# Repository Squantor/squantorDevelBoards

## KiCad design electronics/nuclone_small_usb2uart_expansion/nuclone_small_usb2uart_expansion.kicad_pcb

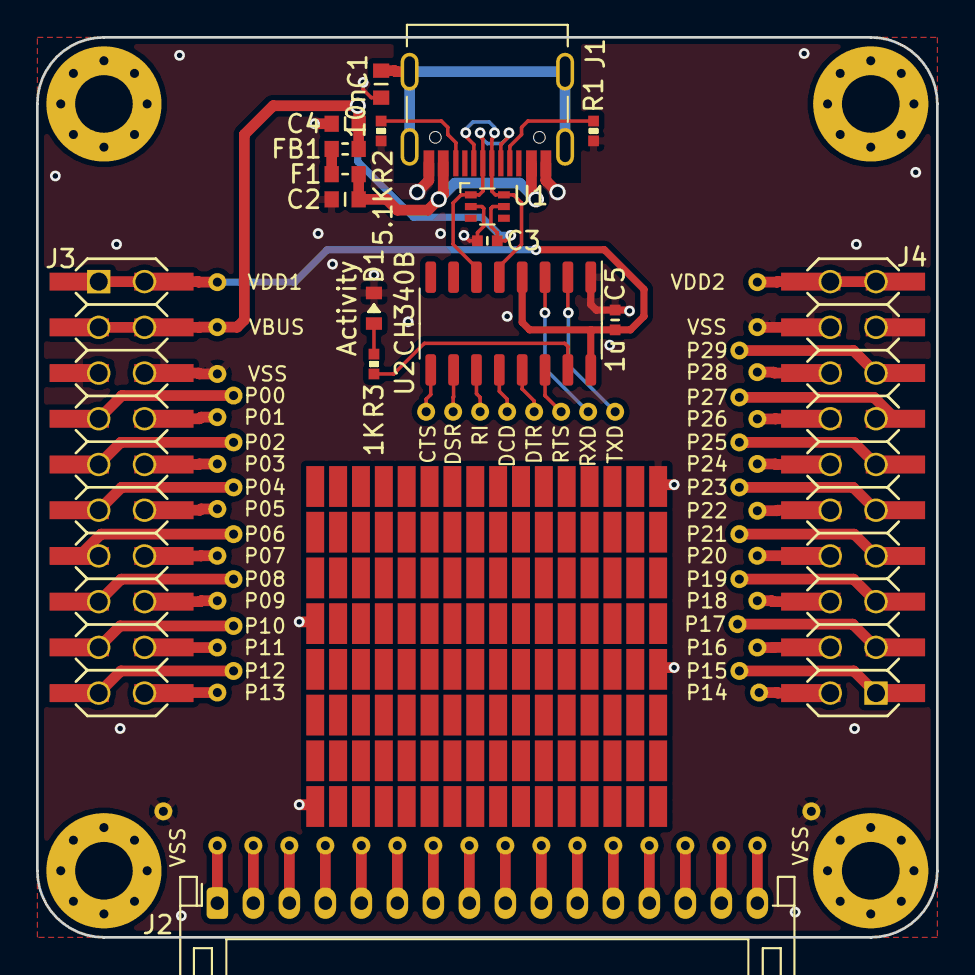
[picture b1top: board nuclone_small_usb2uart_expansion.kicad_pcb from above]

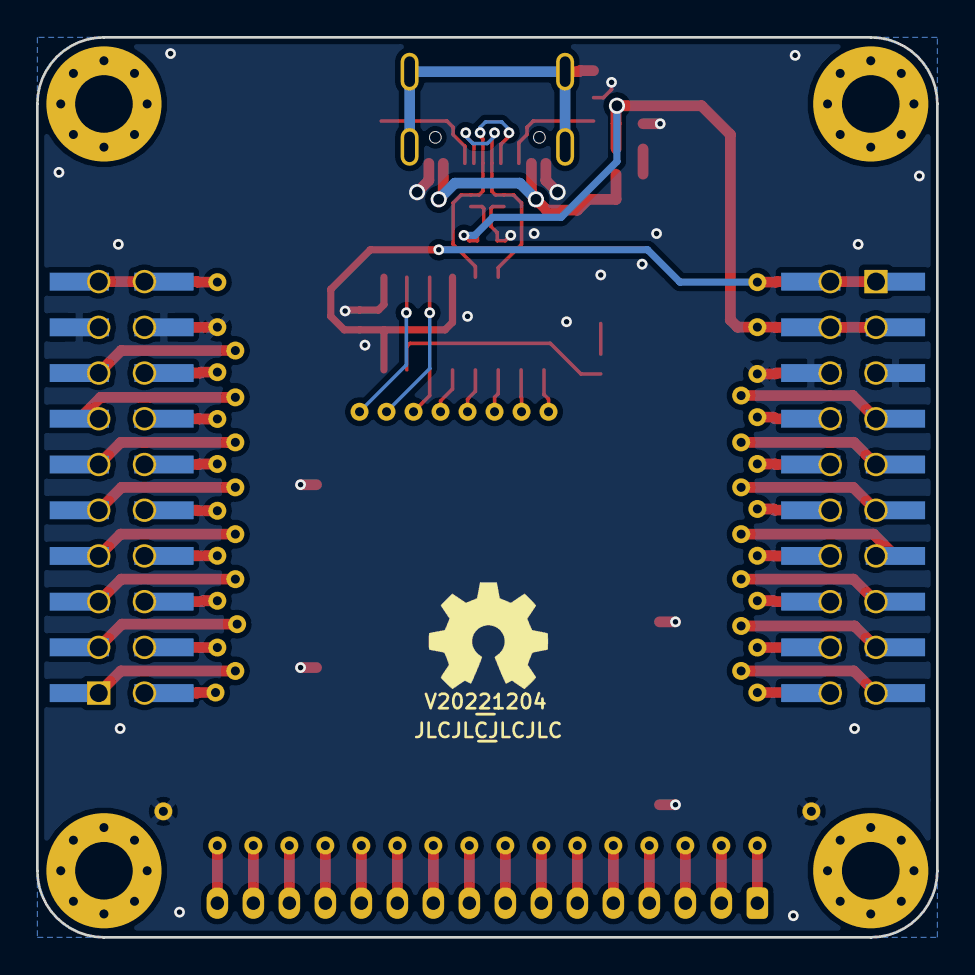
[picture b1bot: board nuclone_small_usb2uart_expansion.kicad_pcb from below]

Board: 2 copper layers, 50.0 x 50.0 mm, 89 parts (3 on the bottom side), 67 nets.

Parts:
C1: 10n; C_0603
C2: 100n; C_0603
C3, C5: 1u; C_0402
C4: 10u; C_0603
D1: Activity; LED_0603_hand
F1: 0.5A; F_0603_hand
FB1: 600; L_0603
H1, H2, H3, H4: MountingHole; MountingHole_3.2mm_M3_Pad_Via
J1: USB-C_PD_USB; USB-C-HRO-31-M-12
J2: Conn_01x16; JST_PH_S16B-PH-K_1x16_P2.00mm_Horizontal
J3: nuclone_small_left; nuclone_small_left_stacked
J4: nuclone_small_right; nuclone_small_right_stacked
J5, J6, J7, J8: 127; proto-SMD-0127-08X08-P010X020+pad
N1: OHWLOGO; OSHW-Symbol_6.7x6mm_SilkScreen
N2: V20221204; Label_Generic
N3: JLCJLCJLCJLC; Label_Generic
R1, R2: 5.1K; R_0402_hand
R3: 1K; R_0402_hand
TP1: VDD1; TestPoint_hole_H05R10_small_text
TP2: VBUS; TestPoint_hole_H05R10_small_text
TP3, TP19, TP60, TP61: VSS; TestPoint_hole_H05R10_small_text
TP4: P00; TestPoint_hole_H05R10_small_text
TP5: P01; TestPoint_hole_H05R10_small_text
TP6: P02; TestPoint_hole_H05R10_small_text
TP7: P03; TestPoint_hole_H05R10_small_text
TP8: P04; TestPoint_hole_H05R10_small_text
TP9: P05; TestPoint_hole_H05R10_small_text
TP10: P06; TestPoint_hole_H05R10_small_text
TP11: P07; TestPoint_hole_H05R10_small_text
TP12: P08; TestPoint_hole_H05R10_small_text
TP13: P09; TestPoint_hole_H05R10_small_text
TP14: P10; TestPoint_hole_H05R10_small_text
TP15: P11; TestPoint_hole_H05R10_small_text
TP16: P12; TestPoint_hole_H05R10_small_text
TP17: P13; TestPoint_hole_H05R10_small_text
TP18: VDD2; TestPoint_hole_H05R10_small_text
TP20: P29; TestPoint_hole_H05R10_small_text
TP21: P28; TestPoint_hole_H05R10_small_text
TP22: P27; TestPoint_hole_H05R10_small_text
TP23: P26; TestPoint_hole_H05R10_small_text
TP24: P25; TestPoint_hole_H05R10_small_text
TP25: P24; TestPoint_hole_H05R10_small_text
TP26: P23; TestPoint_hole_H05R10_small_text
TP27: P22; TestPoint_hole_H05R10_small_text
TP28: P21; TestPoint_hole_H05R10_small_text
TP29: P20; TestPoint_hole_H05R10_small_text
TP30: P19; TestPoint_hole_H05R10_small_text
TP31: P18; TestPoint_hole_H05R10_small_text
TP32: P17; TestPoint_hole_H05R10_small_text
TP33: P16; TestPoint_hole_H05R10_small_text
TP34: P15; TestPoint_hole_H05R10_small_text
TP35: P14; TestPoint_hole_H05R10_small_text
TP36: TXD; TestPoint_hole_H05R10_small_text
TP37: RXD; TestPoint_hole_H05R10_small_text
TP38: RTS; TestPoint_hole_H05R10_small_text
TP39: DTR; TestPoint_hole_H05R10_small_text
TP40: DCD; TestPoint_hole_H05R10_small_text
TP41: RI; TestPoint_hole_H05R10_small_text
TP42: DSR; TestPoint_hole_H05R10_small_text
TP43: CTS; TestPoint_hole_H05R10_small_text
TP44: PH1; TestPoint_hole_H05R10_small_text
TP45: PH2; TestPoint_hole_H05R10_small_text
TP46: PH3; TestPoint_hole_H05R10_small_text
TP47: PH4; TestPoint_hole_H05R10_small_text
TP48: PH5; TestPoint_hole_H05R10_small_text
TP49: PH6; TestPoint_hole_H05R10_small_text
TP50: PH7; TestPoint_hole_H05R10_small_text
TP51: PH8; TestPoint_hole_H05R10_small_text
TP52: PH9; TestPoint_hole_H05R10_small_text
TP53: PH10; TestPoint_hole_H05R10_small_text
TP54: PH11; TestPoint_hole_H05R10_small_text
TP55: PH12; TestPoint_hole_H05R10_small_text
TP56: PH13; TestPoint_hole_H05R10_small_text
TP57: PH14; TestPoint_hole_H05R10_small_text
TP58: PH15; TestPoint_hole_H05R10_small_text
TP59: PH16; TestPoint_hole_H05R10_small_text
U1: TPESD0504C6; SOT363-ONsemi
U2: CH340B; SO-16_3.9x9.9mm_P1.27mm

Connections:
/CC1: J1.A5 (CC1), R1.2
/CC2: J1.B5 (CC2), R2.2
/CTS: TP43.1, U2.9 (CTS#)
/DCD: TP40.1, U2.12 (DCD#)
/DN: J1.A7 (DN1), J1.B7 (DN2), U1.1 (IO_1), U2.6 (UD-)
/DP: J1.A6 (DP1), J1.B6 (DP2), U1.6 (IO_4), U2.5 (UD+)
/DSR: TP42.1, U2.10 (DSR#)
/DTR: TP39.1, U2.13 (DTR#)
/GPIO_00: J3.7 (GPIO_00), TP4.1
/GPIO_01: J3.8 (GPIO_01), TP5.1
/GPIO_02: J3.9 (GPIO_02), TP6.1
/GPIO_03: J3.10 (GPIO_03), TP7.1
/GPIO_04: J3.11 (GPIO_04), TP8.1
/GPIO_05: J3.12 (GPIO_05), TP9.1
/GPIO_06: J3.13 (GPIO_06), TP10.1
/GPIO_07: J3.14 (GPIO_07), TP11.1
/GPIO_08: J3.15 (GPIO_08), TP12.1
/GPIO_09: J3.16 (GPIO_09), TP13.1
/GPIO_10: J3.17 (GPIO_10), TP14.1
/GPIO_11: J3.18 (GPIO_11), TP15.1
/GPIO_12: J3.19 (GPIO_12), TP16.1
/GPIO_13: J3.20 (GPIO_13), TP17.1
/GPIO_14: J4.2 (GPIO_14), TP35.1
/GPIO_15: J4.1 (GPIO_15), TP34.1
/GPIO_16: J4.4 (GPIO_16), TP33.1
/GPIO_17: J4.3 (GPIO_17), TP32.1
/GPIO_18: J4.6 (GPIO_18), TP31.1
/GPIO_19: J4.5 (GPIO_19), TP30.1
/GPIO_20: J4.8 (GPIO_20), TP29.1
/GPIO_21: J4.7 (GPIO_21), TP28.1
/GPIO_22: J4.10 (GPIO_22), TP27.1
/GPIO_23: J4.9 (GPIO_23), TP26.1
/GPIO_24: J4.12 (GPIO_24), TP25.1
/GPIO_25: J4.11 (GPIO_25), TP24.1
/GPIO_26: J4.14 (GPIO_26), TP23.1
/GPIO_27: J4.13 (GPIO_27), TP22.1
/GPIO_28: J4.16 (GPIO_28), TP21.1
/GPIO_29: J4.15 (GPIO_29), TP20.1
/RI: TP41.1, U2.11 (RI#)
/RTS: TP38.1, U2.14 (RTS#)
/RXD: TP37.1, U2.3 (RXD)
/TNOW: R3.1, U2.15 (TNOW)
/TXD: TP36.1, U2.2 (TXD)
/VBUS: C3.1, C4.1, FB1.1, J3.3 (VBUS), J3.4 (VBUS), TP2.1, U1.5 (VDD)
/VDD1: C5.1, J3.1 (VDD), J3.2 (VDD), TP1.1, U2.4 (V3), U2.16 (VCC)
/VDD2: J4.19 (VDD), J4.20 (VDD), TP18.1
/VSS: C1.2, C2.2, C3.2, C4.2, C5.2, D1.1 (K), J1.A1B12 (GND), J1.B1A12 (GND), J3.5 (VSS), J3.6 (VSS), J4.17 (VSS), J4.18 (VSS), J5.1, J6.1, J7.1, J8.1, R1.1, R2.1, TP3.1, TP19.1, TP60.1, TP61.1, U1.2 (VSS), U2.1 (GND)
/VUSB: C2.1, F1.2, J1.A4B9 (VBUS), J1.B4A9 (VBUS)
unnamed: C1.1, J1.S (Shield)
unnamed: D1.2 (A), R3.2
unnamed: F1.1, FB1.2
unnamed: J2.1, TP44.1
unnamed: J2.2, TP45.1
unnamed: J2.3, TP46.1
unnamed: J2.4, TP47.1
unnamed: J2.5, TP48.1
unnamed: J2.6, TP49.1
unnamed: J2.7, TP50.1
unnamed: J2.8, TP51.1
unnamed: J2.9, TP52.1
unnamed: J2.10, TP53.1
unnamed: J2.11, TP54.1
unnamed: J2.12, TP55.1
unnamed: J2.13, TP56.1
unnamed: J2.14, TP57.1
unnamed: J2.15, TP58.1
unnamed: J2.16, TP59.1

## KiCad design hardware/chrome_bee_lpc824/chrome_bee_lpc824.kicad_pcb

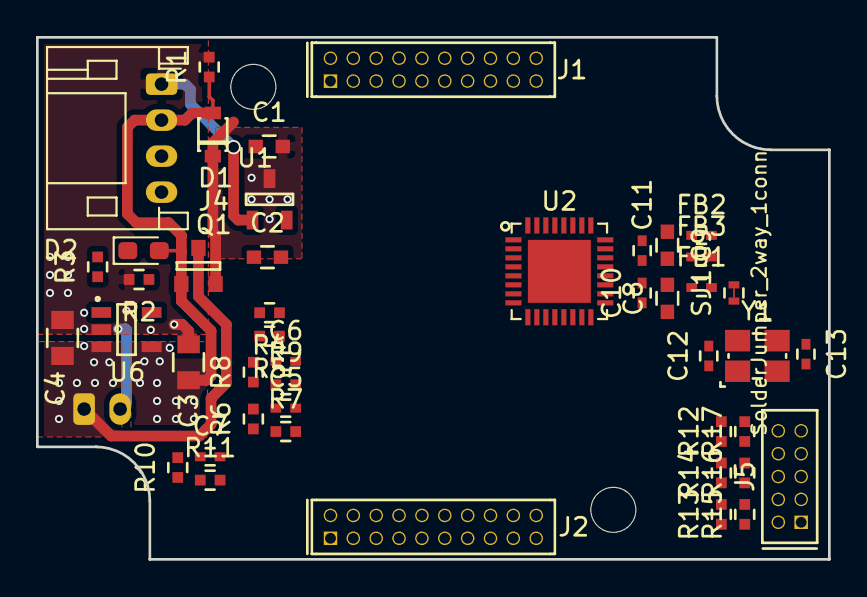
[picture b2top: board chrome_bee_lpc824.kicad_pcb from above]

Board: 2 copper layers, 44.0 x 29.0 mm, 50 parts (1 on the bottom side), 25 nets.

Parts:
C1, C2, C8, C9: 1u; C_0603
C3, C4: 10u; C_0805
C5, C6, C7, C10, C11: 100n; C_0402
C12, C13: 18p; C_0402
D1: NSR0320; SOD_323_onsemi
D2: LED; LED_0603_1608Metric_Pad1.05x0.95mm_HandSolder
FB1, FB2, FB3: FB; C_0402
J1: DevBoardDigital; Header-0127-2X10-H006
J2: DevBoardAnalog; Header-0127-2X10-H006
J3: Battery_2pin; JST_PH_S2B-PH-K_1x02_P2.00mm_Horizontal
J4: DevBoardUartInput; JST_PH_S4B-PH-K_1x04_P2.00mm_Horizontal
J5: JTAG_2X05; Header-0127-2X05-H006
MH1, MH2: MountingHole; MountingHole_2.5mm_no_metal
N1: OHWLOGO; OSHW-Symbol_6.7x6mm_SilkScreen
N2: 20190412; Label_version
Q1: DMP3098L; SOT23-3
R1, R12: 100K; R_0402_hand
R2: 22K; R_0402_hand
R3: 1k; R_0402_hand
R4, R5: 33; R_0402_hand
R6, R7, R8, R9, R10, R11: 1M; R_0402_hand
R13, R14: 100k; R_0402_hand
R15, R16, R17: 100; R_0402_hand
SJ1: SolderJumper_2way_1conn; solder_jumper_2way_conn
U1: MCP1702-MB; SOT23-3-Microchip-TT
U2: LPC824M201JHI33; SOT617-3_alt_paste
U6: MCP738312-OT; SOT23-5-Microchip-OT
Y1: 12MHz; Crystal_3225_4

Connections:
/ADC_VBAT: C7.1, R10.2, R11.1
/ADC_VBUS: C6.1, R8.2, R9.1
/ADC_VIN: C5.1, R6.2, R7.1
/PIO0_2: R13.2, R15.2, U2.7
/PIO0_3: R14.2, R16.2, U2.6
/PIO0_8: C13.1, U2.18, Y1.3
/PIO0_9: C12.1, U2.17, Y1.1
/RESET: R12.2, R17.2, U2.3
/VBAT: C4.1, J2.3, J2.4, J3.1, Q1.3, R10.1, U6.3
/VBUS: C1.2, D1.1, J2.1, J2.2, Q1.2, R8.1, U1.3
/VDD: C2.2, J1.1, J1.2, J2.5, J2.6, J5.1, R12.1, R13.1, SJ1.1, U1.2
/VIN: C3.1, D1.2, D2.2, J4.2, Q1.1, R1.1, R6.1, U6.4
/VSS: C1.1, C2.1, C3.2, C4.2, C5.2, C6.2, C7.2, C8.2, C10.2, C12.2, C13.2, FB3.2, J1.3, J1.4, J2.7, J2.8, J3.2, J4.1, J5.3, J5.5, J5.9, R1.2, R2.2, R7.2, R9.2, R11.2, R14.1, U1.1, U2.33, U6.2, Y1.2, Y1.4
unnamed: C8.1, C10.1, FB1.1, U2.19
unnamed: C9.1, C11.1, FB2.1, U2.21
unnamed: C9.2, C11.2, FB3.1, U2.20
unnamed: D2.1, R3.2
unnamed: FB1.2, FB2.2, SJ1.2
unnamed: J4.3, R4.2
unnamed: J4.4, R5.2
unnamed: J5.2, R15.1
unnamed: J5.4, R16.1
unnamed: J5.10, R17.1
unnamed: R2.1, U6.5
unnamed: R3.1, U6.1

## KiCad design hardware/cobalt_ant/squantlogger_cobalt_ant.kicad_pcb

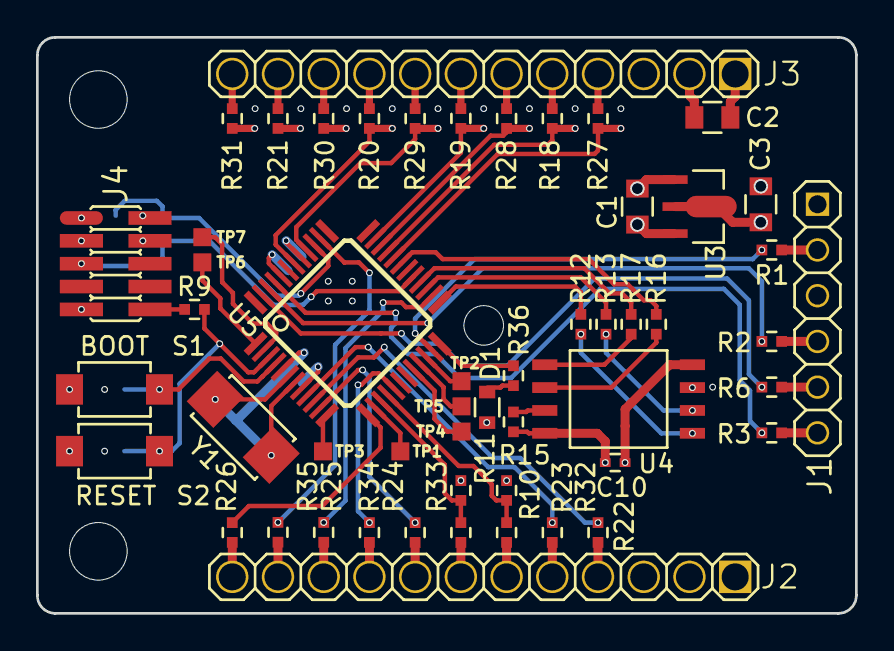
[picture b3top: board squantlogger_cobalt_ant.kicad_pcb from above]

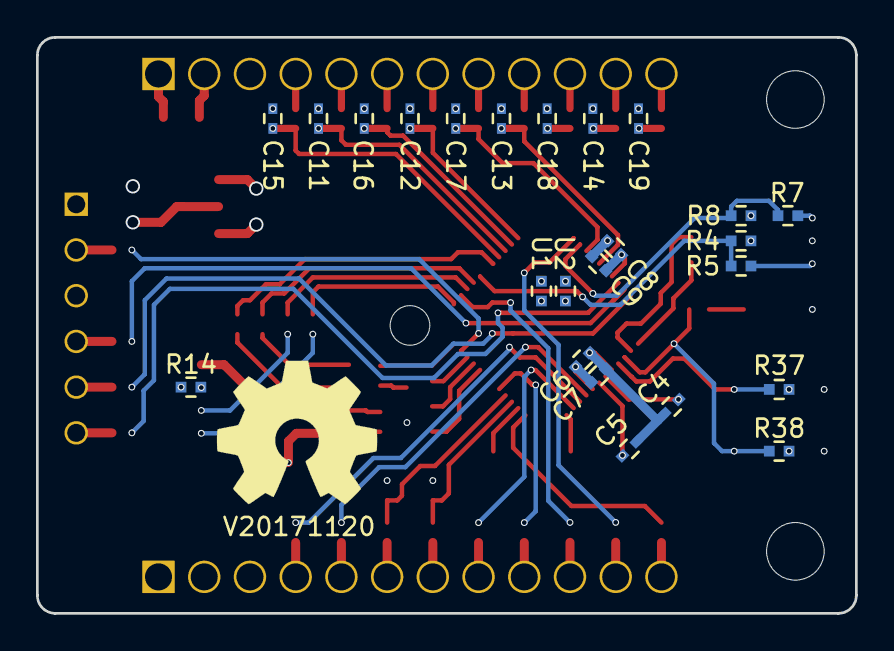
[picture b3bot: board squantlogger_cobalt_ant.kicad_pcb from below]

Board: 4 copper layers, 45.5 x 32.0 mm, 82 parts (26 on the bottom side), 77 nets.

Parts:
C1, C2: 10u; C_0805
C3: 1u; C_0805
C4, C5: 18p; C_0402
C6, C8, C10: 10n; C_0402
C7, C9: 1u; C_0402
C11, C12, C13, C14, C15, C16, C17, C18, C19: C; C_0402
D1: LED; R_0603_hand
H1: Drill_Hole_no_metal; MountingHole_2.2mm_no_metal
H2, H3: Drill_Hole_no_metal; MountingHole_3.2mm_no_metal
J1: FTDI_PINS_1X06; Header-0254-1X06-H010
J2: Cobalt_Ant_Digital; Header-0254-1X12-H015
J3: Cobalt_Ant_Analog; Header-0254-1X12-H015
J4: JTAG_2X05; Header-0127-2X05-SMD
N1: OHWLOGO; OSHW-Symbol_8.9x8mm_SilkScreen
N2: V20171120; Label_version
R1, R2, R3, R6, R18, R19, R20, R21, R22, R23, R24, R25, R26, R27, R28, R29, R30, R31, R32, R33, R34, R35: 100; R_0402_hand
R4, R8, R9, R12, R13, R16, R17: 33; R_0402_hand
R5, R7, R37, R38: 10k; R_0402_hand
R10, R11: 2K2; R_0402_hand
R14, R15: 10K; R_0402_hand
R36: 4.7k; R_0402_hand
S1: BOOT; TD-85XU
S2: RESET; TD-85XU
TP1, TP2, TP3, TP4, TP5, TP6, TP7: testpad; TESTPAD_SQ_1MM
U1, U2: POWER_JOINER; R_0402_hand
U3: MCP1702-MB; MB-(SOT-89)
U4: W25Q32BV; WINBOND_SS
U5: LPC1114FBD48/302; SOT313-2
Y1: 12.0MHz; X_5.0_3.2

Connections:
+BATT: C3.1, J1.3, J2.1, U3.2, U3.TAB
ADC_0: C15.1, R27.1, U5.32
ADC_1: C11.1, R18.1, U5.33
ADC_2: C16.1, R28.1, U5.34
ADC_3: C12.1, R19.1, U5.35
ADC_4: C17.1, R29.1, U5.40
ADC_5: C13.1, R20.1, U5.42
ADC_6: C18.1, R30.1
ADC_7: C14.1, R21.1
ADC_8: C19.1, R31.1
BOOT: R37.2, S1.2, U5.4
FLASH_CE: R12.2, U5.25
FLASH_MISO: R13.2, U5.27
FLASH_MOSI: R17.1, U5.28
FLASH_SCK: R16.1, U5.31
GND: C1.2, C3.2, C4.1, C5.1, C6.1, C7.2, C10.2, J1.1, J2.2, J4.3, J4.5, J4.9, R5.1, S1.1, S2.1, U1.1, U3.1, U4.4, U5.5
GNDA: C2.2, C8.2, C9.2, C12.2, C13.2, C14.2, C15.2, C16.2, C17.2, C18.2, C19.2, J3.1, U1.2, U5.41
GPIO0_2: R22.1, U5.10
GPIO1_8: R32.1, U5.9
GPIO1_9: R34.1, U5.17
GPIO2_7: R24.1, U5.11
I2C_SCL: R11.2, R33.1, U5.15
I2C_SDA: R10.2, R23.1, U5.16
LED: R36.2, U5.24
unnamed: C4.2, U5.6, Y1.1
unnamed: C5.2, U5.7, Y1.2
unnamed: D1.1, R36.1
unnamed: J1.2, R1.2
unnamed: J1.4, R2.2
unnamed: J1.5, R6.2
unnamed: J1.6, R3.2
unnamed: J2.4, R22.2
unnamed: J2.5, R32.2
unnamed: J2.6, R23.2
unnamed: J2.7, R33.2
unnamed: J2.8, R24.2
unnamed: J2.9, R34.2
unnamed: J2.10, R25.2
unnamed: J2.11, R35.2
unnamed: J2.12, R26.2
unnamed: J3.4, R27.2
unnamed: J3.5, R18.2
unnamed: J3.6, R28.2
unnamed: J3.7, R19.2
unnamed: J3.8, R29.2
unnamed: J3.9, R20.2
unnamed: J3.10, R30.2
unnamed: J3.11, R21.2
unnamed: J3.12, R31.2
unnamed: J4.2, R8.1
unnamed: J4.4, R4.1
unnamed: J4.10, R9.1
unnamed: R12.1, U4.1
unnamed: R13.1, U4.2
unnamed: R14.1, U4.3
unnamed: R15.2, U4.7
unnamed: R16.2, U4.6
unnamed: R17.2, U4.5
unnamed: TP1.1, U5.14
unnamed: TP2.1, U5.22
unnamed: TP3.1, U5.12
unnamed: TP4.1, U5.20
unnamed: TP5.1, U5.21
unnamed: TP6.1, U5.1
unnamed: TP7.1, U5.2
SERIAL_CTS: R1.1, U5.23
SERIAL_RTS: R3.1, U5.45
SERIAL_RXD: R6.1, U5.47
SERIAL_TXD: R2.1, U5.46
SPI_MISO: R25.1, U5.26
SPI_MOSI: R35.1, U5.38
SPI_SCK: R26.1, U5.13
SWDCLK: R4.2, R5.2, U5.29
SWDIO: R7.2, R8.2, U5.39
VDD: C1.1, C6.2, C7.1, C10.1, D1.2, J2.3, J4.1, R7.1, R10.1, R11.1, R14.2, R15.1, R37.1, R38.1, U2.1, U3.3, U4.8, U5.8
VDDA: C2.1, C8.1, C9.1, J3.2, J3.3, U2.2, U5.44
nRESET: R9.2, R38.2, S2.2, U5.3

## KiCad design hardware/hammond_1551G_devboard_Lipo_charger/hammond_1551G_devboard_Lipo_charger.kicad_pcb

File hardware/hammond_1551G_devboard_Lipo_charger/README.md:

# Hammond 1551G development board Lithium Polymer charger
This development board fits a [Hammond 1551G project box](http://www.hammondmfg.com/pdf/1551G.pdf) and contains a lithium polymer charger and some other connections for testing.
## TODO's
Still some things need to be done:
* schematic entry and component definitions (Done)
* PCB layout (Done)
* Review with one night in between (Done)
* Produce at [OSHPARK](https://oshpark.com/) (in progress)
* Assemble
* Test & characterise
* update Readme.md with pictures and BOM
## BOM
## Pictures

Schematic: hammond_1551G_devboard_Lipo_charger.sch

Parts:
C1: 1u; C_0805
C2, C3, C4: 10u; C_0805
D1: NSR0320; SOD_323_onsemi
D2: LED; LED_0603_1608Metric_Pad1.05x0.95mm_HandSolder
J1: DevBoardDigital; Header-0127-2X10-H006
J2: DevBoardAnalog; Header-0127-2X10-H006
J3: Battery_2pin; JST_PH_S2B-PH-K_1x02_P2.00mm_Horizontal
J4: DevBoardUartInput; JST_PH_S4B-PH-K_1x04_P2.00mm_Horizontal
J5, J7: Proto; proto-TH-0127-04X04-P010-H006
J6: Proto; proto-TH-0254-09X05-P020SQ-H010
MH1, MH2: MountingHole; MountingHole_2.5mm_no_metal
N1: OHWLOGO; OSHW-Symbol_6.7x6mm_SilkScreen
N2: 20190210; Label_version
Q1: DMP3098L; SOT23-3
R1: 100K; R_0603_hand
R2: 22K; R_0603_hand
R3: 1k; R_0603_hand
U1: MCP1702-MB; SOT23-3-Microchip-TT
U2, U3, U4, U5: power_joiner_2_nets; power_joiner_2_conn_06mm
U6: MCP738312-OT; SOT23-5-Microchip-OT

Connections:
+BATT: C4.1, J2.3 (VBAT), J2.4 (VBAT), J3.1 (VBAT+_IN), Q1.3 (D), U6.3 (VBAT)
/VIN: C3.1, D1.2 (A), D2.2 (A), J4.2 (VBUS), Q1.1 (G), R1.1, U6.4 (VDD)
GND: C1.1, C2.1, C3.2, C4.2, J3.2 (VBAT-_IN), J4.1 (GND), R1.2, R2.2, U1.1, U2.1, U3.1, U6.2 (VSS)
unnamed: C2.2, U1.2, U4.1, U5.1
unnamed: D2.1 (K), R3.2
unnamed: R2.1, U6.5 (PROG)
unnamed: R3.1, U6.1 (STAT)
VBUS: C1.2, D1.1 (K), J2.1 (VBUS), J2.2 (VBUS), Q1.2 (S), U1.3
VDD: J1.1 (VDD), J1.2 (VDD), U5.2
VDDA: J2.5 (VDDA), J2.6 (VDDA), U4.2
VSS: J1.3 (VSS), J1.4 (VSS), U2.2
VSSA: J2.7 (VSSA), J2.8 (VSSA), U3.2

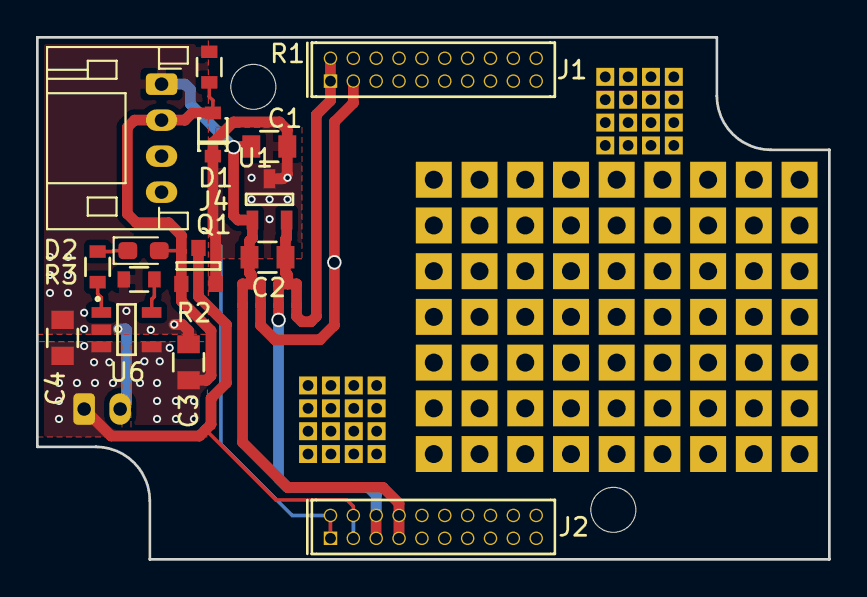
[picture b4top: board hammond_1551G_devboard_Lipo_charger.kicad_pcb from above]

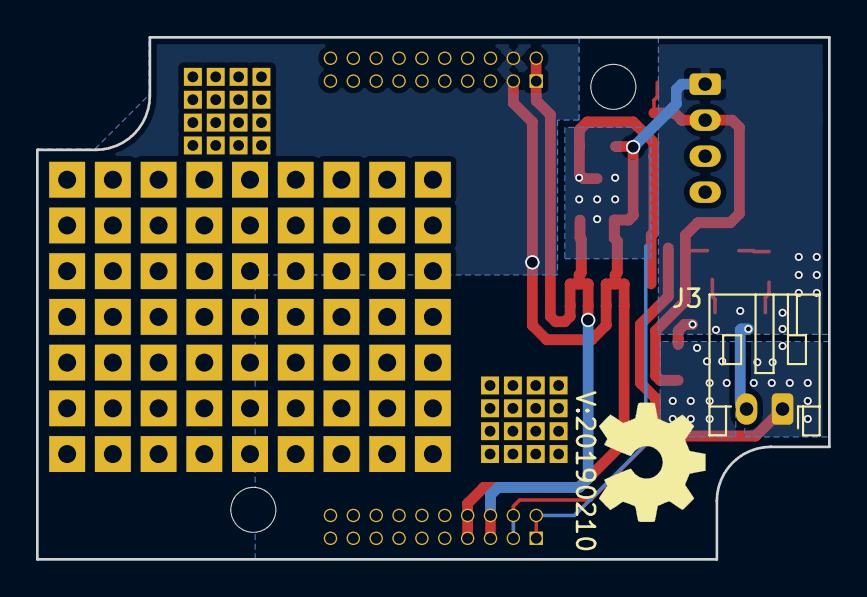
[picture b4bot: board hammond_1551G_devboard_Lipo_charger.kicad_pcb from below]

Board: 2 copper layers, 44.0 x 29.0 mm, 27 parts (2 on the bottom side), 12 nets.

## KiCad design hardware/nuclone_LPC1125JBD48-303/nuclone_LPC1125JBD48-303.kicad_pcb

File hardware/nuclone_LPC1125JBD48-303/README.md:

# Nuclone development board for LPC1125JBD48/303
LPC1125JBD48 development board inspired by the nucleo series from STM32.
## TODO's
Still some things need to be done:
* schematic entry (WIP)
* PCB layout (WIP)
* Review with one night in between (TODO)
* Produce at [JLCPCB](https://jlcpcb.com/) (TODO)
* Assemble (TODO)
* Test & characterise (TODO)
* update Readme.md with pictures and BOM (TODO)

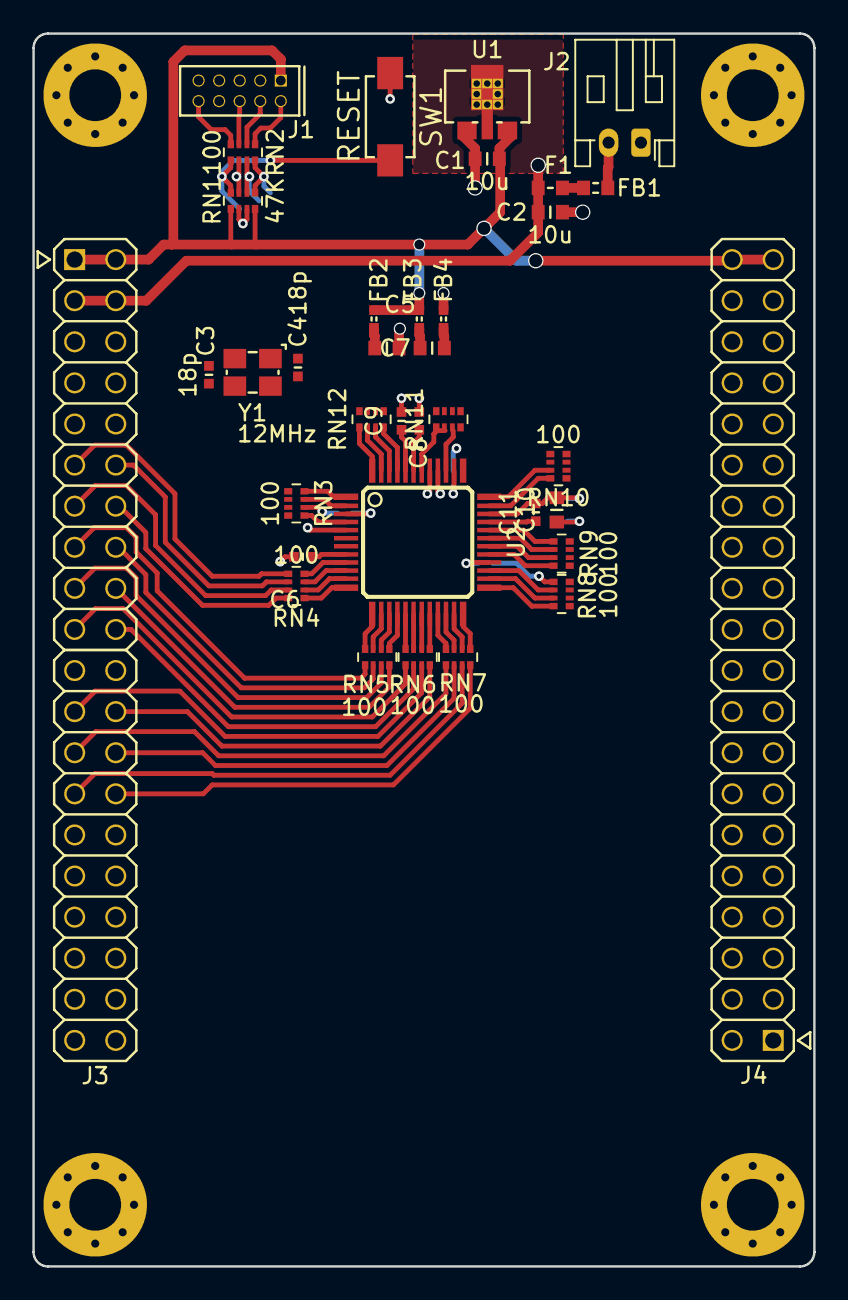
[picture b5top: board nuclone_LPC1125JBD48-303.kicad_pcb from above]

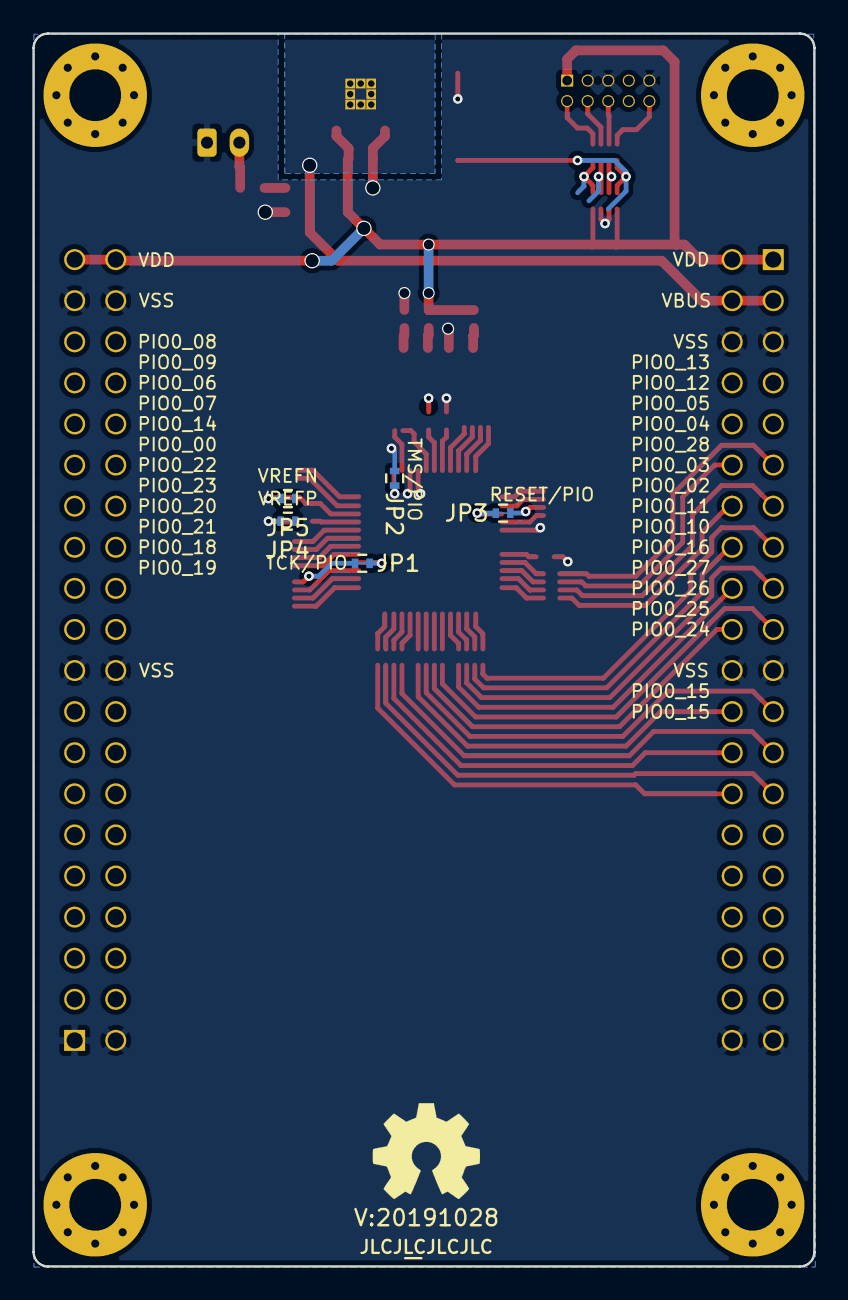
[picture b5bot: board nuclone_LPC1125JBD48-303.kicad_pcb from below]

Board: 2 copper layers, 48.3 x 76.2 mm, 48 parts (8 on the bottom side), 96 nets.

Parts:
C1, C2, C5, C7, C10: 10u; C_0603
C3, C4: 18p; C_0402
C6, C8, C9, C11: 1u; C_0402
F1: 0.5A; F_0603_hand
FB1: 100; L_0603
FB2, FB3, FB4: FB; L_0402
H1, H2, H3, H4: MountingHole; MountingHole_3.2mm_M3_Pad_Via
J1: JTAG_2X05; Header-0127-2X05-H006
J2: Conn_01x02; JST_PH_S2B-PH-K_1x02_P2.00mm_Horizontal
J3: nuclone_small_left; nuclone_medium_left
J4: nuclone_small_right; nuclone_medium_right
JP1: TCK/PIO; solder_jumper_2way_conn
JP2: TMS/PIO; solder_jumper_2way_conn
JP3: RESET/PIO; solder_jumper_2way_conn
JP4: VREFP; solder_jumper_2way_conn
JP5: VREFN; solder_jumper_2way_conn
N1: OHWLOGO; OSHW-Symbol_6.7x6mm_SilkScreen
N2: 20191028; Label_version
N3: JLCJLCJLCJLC; Label_Generic
RN1: 47K; R_Array_Convex_4x0402
RN2, RN3, RN4, RN5, RN6, RN7, RN8, RN9, RN10, RN11, RN12: 100; R_Array_Convex_4x0402
SW1: RESET; DTSM3
U1: MCP1702-MB; SOT89-SOT23-Dual-NXP
U2: LPC1125JBD48_303; SOT313-2-NXP
Y1: 12MHz; Crystal_3225_4

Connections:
/PIO0_0: JP3.1, RN3.2
/PIO0_0_MCU: JP3.2, RN1.8, RN2.5, SW1.2, U2.3
/PIO0_0_OUT: J3.9, RN3.7
/PIO0_1_MCU: RN3.1, U2.4
/PIO0_1_OUT: J3.10, RN3.8
/PIO0_2_MCU: RN4.3, U2.10
/PIO0_2_OUT: J3.12, RN4.6
/PIO0_3_MCU: RN5.3, U2.14
/PIO0_3_OUT: J3.16, RN5.6
/PIO0_4_MCU: RN5.2, U2.15
/PIO0_4_OUT: J3.17, RN5.7
/PIO0_5_MCU: RN5.1, U2.16
/PIO0_5_OUT: J3.18, RN5.8
/PIO0_6_MCU: RN7.3, U2.22
/PIO0_6_OUT: J3.26, RN7.6
/PIO0_7_MCU: RN7.2, U2.23
/PIO0_7_OUT: J3.27, RN7.7
/PIO0_8_MCU: RN8.3, U2.26
/PIO0_8_OUT: J4.18, RN8.6
/PIO0_9_MCU: RN8.2, U2.27
/PIO0_9_OUT: J4.21, RN8.7
/PIO0_10: JP1.1, RN8.1
/PIO0_10_MCU: JP1.2, RN1.6, RN2.7, U2.28
/PIO0_10_OUT: J4.22, RN8.8
/PIO0_11_MCU: RN9.3, U2.30
/PIO0_11_OUT: J4.24, RN9.6
/PIO1_0_MCU: RN9.2, U2.31
/PIO1_0_OUT: J4.25, RN9.7
/PIO1_1_MCU: RN9.1, U2.32
/PIO1_1_OUT: J4.26, RN9.8
/PIO1_2_MCU: RN10.4, U2.35
/PIO1_2_OUT: J4.27, RN10.5
/PIO1_3: JP2.1, RN11.3
/PIO1_3_MCU: JP2.2, RN1.5, RN2.8, U2.38
/PIO1_3_OUT: J4.30, RN11.6
/PIO1_4_MCU: RN11.2, U2.39
/PIO1_4_OUT: J4.31, RN11.7
/PIO1_5_MCU: RN12.4, U2.45
/PIO1_5_OUT: J4.33, RN12.5
/PIO1_6_MCU: RN12.3, U2.46
/PIO1_6_OUT: J4.34, RN12.6
/PIO1_7_MCU: RN12.2, U2.47
/PIO1_7_OUT: J4.35, RN12.7
/PIO1_8_MCU: RN4.4, U2.9
/PIO1_8_OUT: J3.11, RN4.5
/PIO1_9_MCU: RN6.4, U2.17
/PIO1_9_OUT: J3.19, RN6.5
/PIO1_10_MCU: RN9.4, U2.29
/PIO1_10_OUT: J4.23, RN9.5
/PIO1_11_MCU: RN11.1, U2.42
/PIO1_11_OUT: J4.32, RN11.8
/PIO2_0_MCU: RN3.3, U2.2
/PIO2_0_OUT: J3.8, RN3.6
/PIO2_1_MCU: RN5.4, U2.13
/PIO2_1_OUT: J3.15, RN5.5
/PIO2_2_MCU: RN8.4, U2.25
/PIO2_2_OUT: J4.17, RN8.5
/PIO2_3_MCU: RN11.4, U2.37
/PIO2_3_OUT: J4.29, RN11.5
/PIO2_4_MCU: RN6.2, U2.19
/PIO2_4_OUT: J3.23, RN6.7
/PIO2_5_MCU: RN6.1, U2.20
/PIO2_5_OUT: J3.24, RN6.8
/PIO2_6_MCU: RN3.4, U2.1
/PIO2_6_OUT: J3.7, RN3.5
/PIO2_7_MCU: RN4.2, U2.11
/PIO2_7_OUT: J3.13, RN4.7
/PIO2_8_MCU: RN4.1, U2.12
/PIO2_8_OUT: J3.14, RN4.8
/PIO2_9_MCU: RN7.1, U2.24
/PIO2_9_OUT: J3.28, RN7.8
/PIO3_0_MCU: RN10.3, U2.36
/PIO3_0_OUT: J4.28, RN10.6
/PIO3_3_MCU: RN12.1, U2.48
/PIO3_3_OUT: J4.36, RN12.8
/PIO3_4_MCU: RN6.3, U2.18
/PIO3_4_OUT: J3.20, RN6.6
/PIO3_5_MCU: RN7.4, U2.21
/PIO3_5_OUT: J3.25, RN7.5
/SWO_TDO: RN1.7, RN2.6
/VBUS: C2.2, F1.1, J3.3, J3.4, U1.2
/VDD: C1.1, FB2.2, FB3.2, J1.1, J3.1, J3.2, J4.39, J4.40, RN1.1, RN1.4, U1.3
/VDDA_MCU: C7.1, C8.1, FB3.1, JP4.1, U2.43
/VDD_MCU: C5.1, C6.1, C9.1, FB2.1, U2.8, U2.44
/VREFN_MCU: C10.2, C11.2, JP5.2, U2.34
/VREFP_MCU: C10.1, C11.1, JP4.2, U2.33
/VSSA_MCU: C7.2, C8.2, FB4.1, JP5.1, U2.40
/XTAL_IN: C3.1, U2.6, Y1.1
/XTAL_OUT: C4.1, U2.7, Y1.3
unnamed: F1.2, FB1.1
unnamed: FB1.2, J2.2
unnamed: J1.2, RN2.1
unnamed: J1.4, RN2.2
unnamed: J1.6, RN2.3
unnamed: J1.10, RN2.4
VSS: C1.2, C2.1, C3.2, C4.2, C5.2, C6.2, C9.2, FB4.2, J1.3, J1.5, J1.9, J2.1, J3.5, J3.6, J3.21, J3.22, J3.39, J3.40, J4.1, J4.2, J4.19, J4.20, J4.37, J4.38, RN1.2, RN1.3, SW1.1, U1.1, U2.5, U2.41, Y1.2, Y1.4

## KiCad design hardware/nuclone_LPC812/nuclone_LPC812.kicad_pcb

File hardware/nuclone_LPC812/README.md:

# Nuclone development board for LPC812
LPC812 development board inspired by the nucleo series from STM32.
## TODO's
Still some things need to be done:
* schematic entry (WIP)
* PCB layout (TODO)
* Review with one night in between (TODO)
* Produce at [OSHPARK](https://oshpark.com/) (TODO)
* Assemble (TODO)
* Test & characterise (TODO)
* update Readme.md with pictures and BOM (TODO)

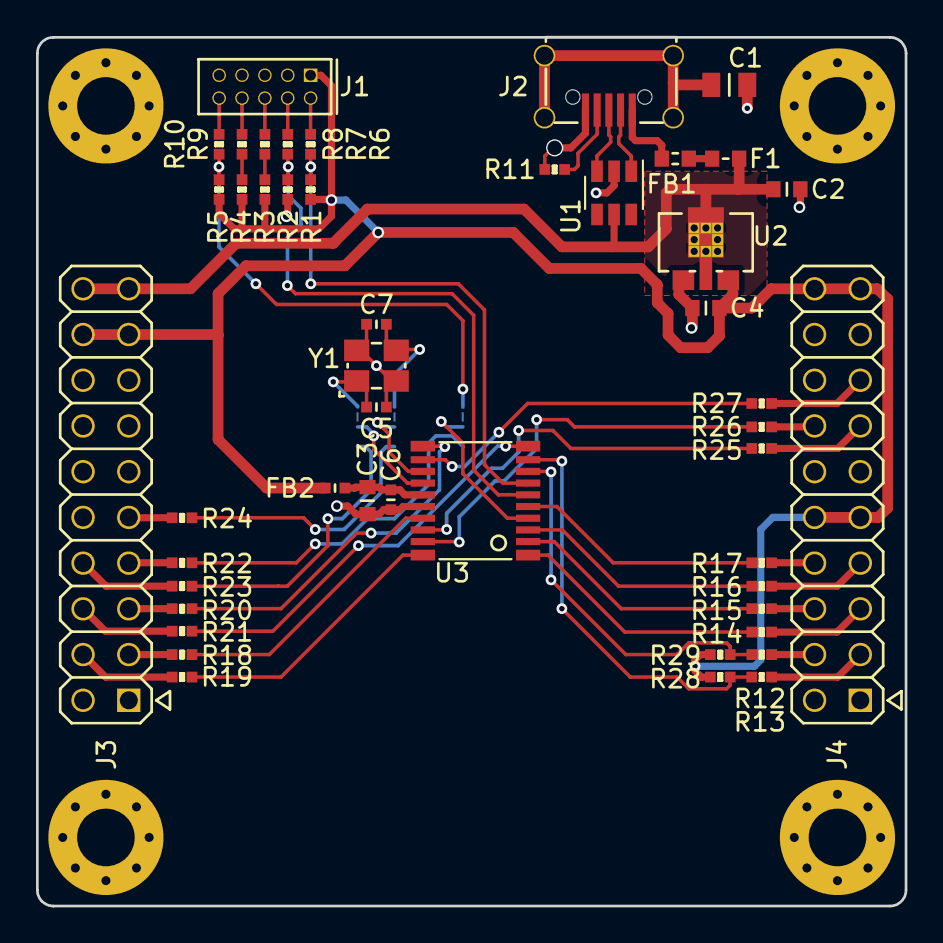
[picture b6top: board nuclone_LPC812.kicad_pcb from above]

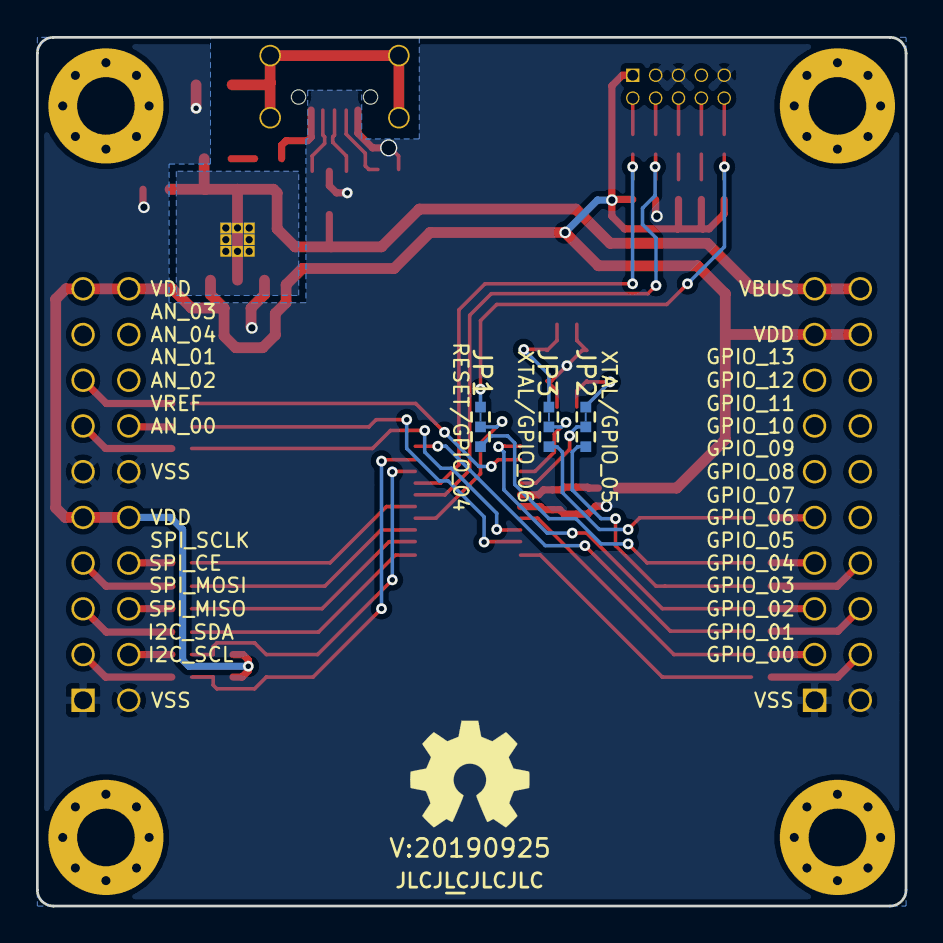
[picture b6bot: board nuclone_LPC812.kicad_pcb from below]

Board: 2 copper layers, 48.3 x 48.3 mm, 57 parts (6 on the bottom side), 57 nets.

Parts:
C1: 100n; C_0805
C2, C3, C4: 10u; C_0603
C5, C7: 18p; C_0402
C6: 1u; C_0402
F1: 0.5A; F_0603_hand
FB1: 100; L_0603
FB2: FB; C_0402
H1, H2, H3, H4: MountingHole; MountingHole_3.2mm_M3_Pad_Via
J1: JTAG_2X05; Header-0127-2X05-H006
J2: USB-ID; USB-muB-SMD_TH
J3: nuclone_20pin_gpio; Nuclone_20pin_gpio
J4: nuclone_20pin_bus_analog; Nuclone_20pin_bus_analog
JP1: RESET/GPIO_04; solder_jumper_3way_23conn
JP2: XTAL/GPIO_05; solder_jumper_3way_23conn
JP3: XTAL/GPIO_06; solder_jumper_3way_23conn
N1: OHWLOGO; OSHW-Symbol_6.7x6mm_SilkScreen
N2: 20190925; Label_version
N3: JLCJLCJLCJLC; Label_Generic
R1, R4: 100K; R_0402_hand
R2, R3, R5: 100k; R_0402_hand
R6, R7, R8, R9, R10, R12, R13, R14, R15, R16, R17, R18, R19, R20, R21, R22, R23, R24, R25, R26, R27: 100; R_0402_hand
R11: 0; R_0402_hand
R28, R29: 2.2K; R_0402_hand
U1: USBLC6-2; SOT23-6-HAND
U2: MCP1702-MB; SOT89-SOT23-Dual-NXP
U3: LPC812M101JDH20; SOT360
Y1: 12MHz; Crystal_3225_4

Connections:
/AN_00: J4.14, R26.2
/AN_01: J4.15, R27.2
/GPIO_00: J3.3, R18.2
/GPIO_01: J3.4, R19.2
/GPIO_02: J3.5, R20.2
/GPIO_03: J3.6, R21.2
/GPIO_04: J3.7, R22.2
/GPIO_05: J3.8, R23.2
/GPIO_06: J3.9, R24.2
/I2C_SCL: J4.4, R13.2
/I2C_SDA: J4.3, R12.2
/Jtag connector/TDI: R4.2, R9.2
/LPC812M101JD20 base/GPIO_04_INT: JP1.1, R22.1
/LPC812M101JD20 base/GPIO_05_INT: JP2.1, R23.1
/LPC812M101JD20 base/GPIO_06_INT: JP3.1, R24.1
/LPC812M101JD20 base/PIO0_0: R26.1, U3.19
/LPC812M101JD20 base/PIO0_1: R27.1, U3.12
/LPC812M101JD20 base/PIO0_4: R17.1, U3.5
/LPC812M101JD20 base/PIO0_5: JP1.2, U3.4
/LPC812M101JD20 base/PIO0_6: R25.1, U3.18
/LPC812M101JD20 base/PIO0_7: R18.1, U3.17
/LPC812M101JD20 base/PIO0_8: JP2.2, U3.14
/LPC812M101JD20 base/PIO0_9: JP3.2, U3.13
/LPC812M101JD20 base/PIO0_10: R12.1, R28.2, U3.9
/LPC812M101JD20 base/PIO0_11: R13.1, R29.2, U3.8
/LPC812M101JD20 base/PIO0_12: R16.1, U3.3
/LPC812M101JD20 base/PIO0_13: R15.1, U3.2
/LPC812M101JD20 base/PIO0_14: R19.1, U3.20
/LPC812M101JD20 base/PIO0_15: R20.1, U3.11
/LPC812M101JD20 base/PIO0_16: R21.1, U3.10
/LPC812M101JD20 base/PIO0_17: R14.1, U3.1
/LPC812M101JD20 base/XTAL_IN: C5.1, JP2.3, Y1.1
/LPC812M101JD20 base/XTAL_OUT: C7.1, JP3.3, Y1.3
/MCU_RESET: JP1.3, R5.2, R10.2
/MCU_TCK: R2.2, R7.2, U3.6
/MCU_TDO: R3.2, R8.2
/MCU_TMS: R1.2, R6.2, U3.7
/SPI_CE: J4.8, R17.2
/SPI_MISO: J4.6, R15.2
/SPI_MOSI: J4.5, R14.2
/SPI_SCLK: J4.7, R16.2
/USB input/USB_IN_D+: J2.3, U1.3
/USB input/USB_IN_D-: J2.2, U1.1
/VBUS: C2.1, F1.1, J3.19, J3.20, U1.5, U2.2
/VDD: C4.1, FB2.2, J1.1, J3.17, J3.18, J4.9, J4.10, J4.19, J4.20, R1.1, R3.1, R4.1, R5.1, R28.1, R29.1, U2.3
/VREF: J4.13, R25.2
unnamed: C1.1, J2.S
unnamed: C3.1, C6.1, FB2.1, U3.15
unnamed: F1.2, FB1.1
unnamed: FB1.2, J2.1
unnamed: J1.2, R6.1
unnamed: J1.4, R7.1
unnamed: J1.6, R8.1
unnamed: J1.8, R9.1
unnamed: J1.10, R10.1
unnamed: J2.4, R11.1
VSS: C1.2, C2.2, C3.2, C4.2, C5.2, C6.2, C7.2, J1.3, J1.5, J1.9, J2.5, J3.1, J3.2, J4.1, J4.2, J4.11, J4.12, R2.1, R11.2, U1.2, U2.1, U3.16, Y1.2, Y1.4
